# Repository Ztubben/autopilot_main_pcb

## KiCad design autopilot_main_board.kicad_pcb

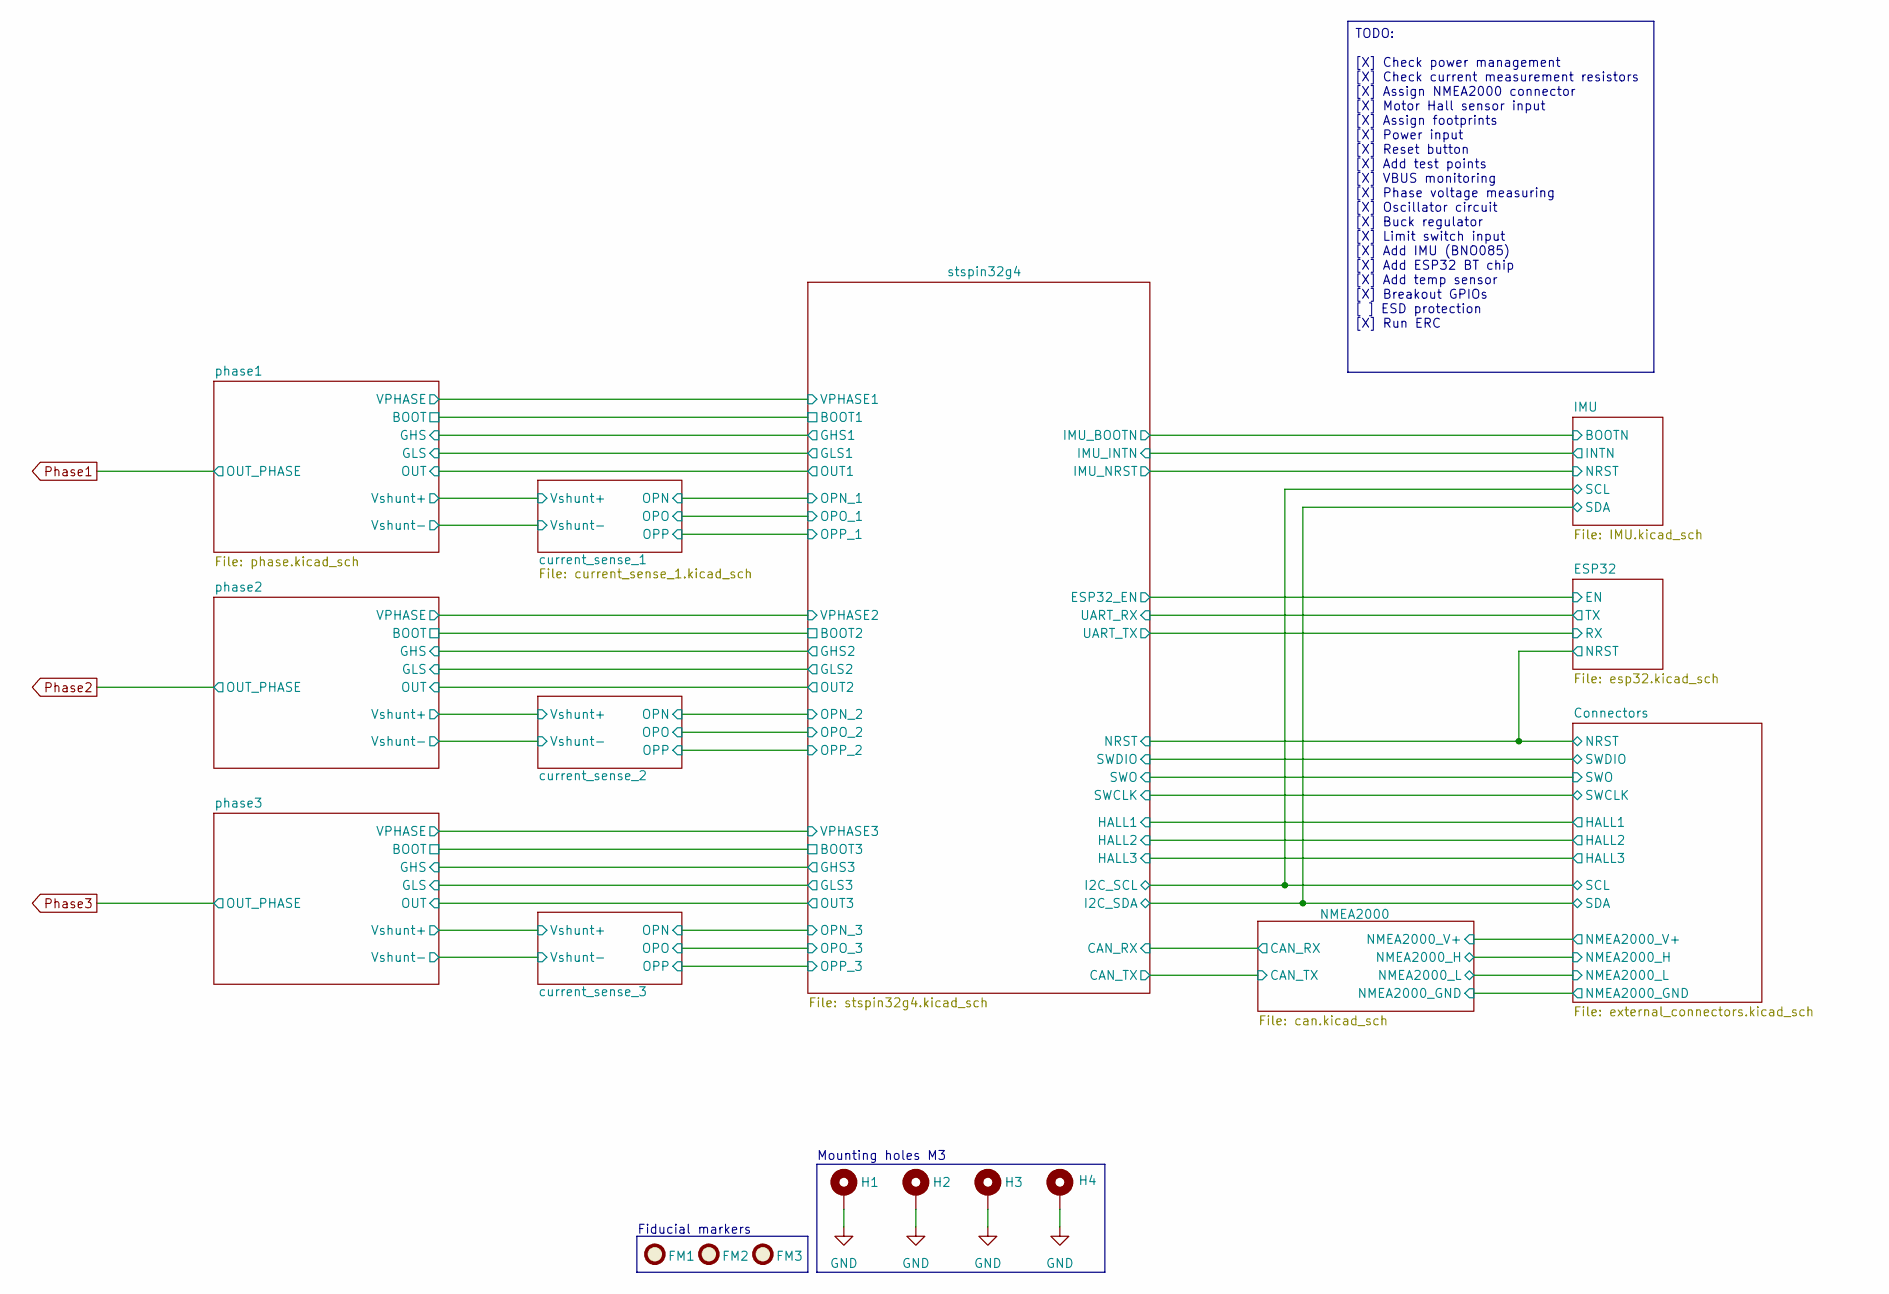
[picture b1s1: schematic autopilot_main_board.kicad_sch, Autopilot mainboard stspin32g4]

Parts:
FM1, FM2, FM3: Fiducial_1mm_Mask2mm
H1, H2, H3, H4: MountingHole_3.2mm_M3_DIN965_Pad

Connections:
GND: H1.1, H2.1, H3.1, H4.1; also elsewhere on the board

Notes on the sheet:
Mounting holes M3
Fiducial markers
TODO: [X] Check power management [X] Check current measurement resistors [X] Assign NMEA2000 connector [X] Motor Hall sensor input [X] Assign footprints [X] Power input [X] Reset button [X] Add test points [X] VBUS monitoring [X] Phase voltage measuring [X] Oscillator circuit [X] Buck regulator [X]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

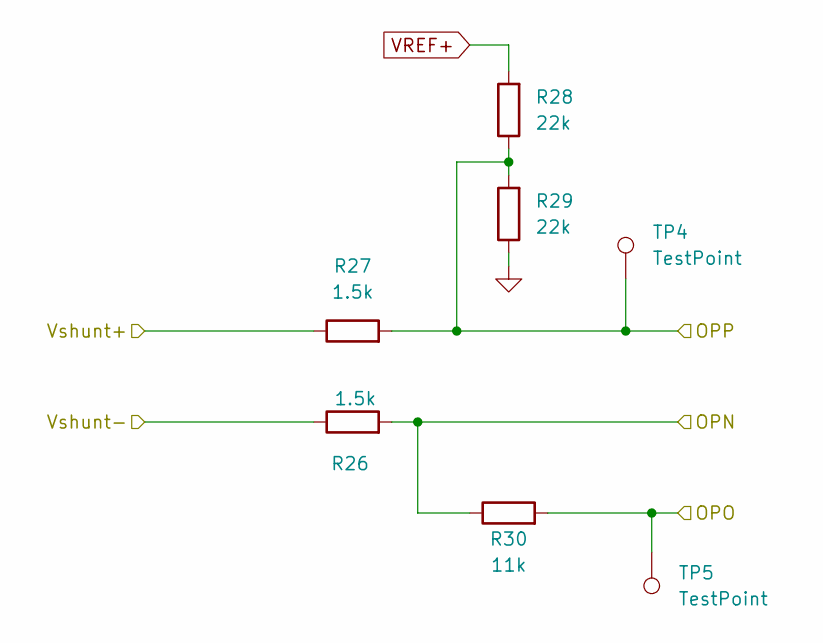
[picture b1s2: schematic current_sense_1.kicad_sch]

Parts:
R26, R27: 1.5k; R_0603_1608Metric
R28, R29: 22k; R_0603_1608Metric
R30: 11k; R_0603_1608Metric
TP4, TP5: TestPoint; TestPoint_Pad_D2.0mm

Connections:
/current_sense_1/OPN: R26.2, R30.1; also elsewhere on the board
/current_sense_1/OPO: R30.2, TP5.1; also elsewhere on the board
/current_sense_1/OPP: R27.2, R28.1, R29.2, TP4.1; also elsewhere on the board
/current_sense_1/Vshunt+: R27.1; also elsewhere on the board
GND: R26.1, R29.1; also elsewhere on the board
VREF+: R28.2; also elsewhere on the board

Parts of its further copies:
R31, R32, R44, R45: 1.5k; R_0603_1608Metric
R33, R34, R46, R47: 22k; R_0603_1608Metric
R35, R48: 11k; R_0603_1608Metric
TP6, TP7, TP8, TP9: TestPoint; TestPoint_Pad_D2.0mm

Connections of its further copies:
/current_sense_2/OPN: R31.2, R35.1; also elsewhere on the board
/current_sense_2/OPO: R35.2, TP7.1; also elsewhere on the board
/current_sense_2/OPP: R32.2, R33.1, R34.2, TP6.1; also elsewhere on the board
/current_sense_2/Vshunt+: R32.1; also elsewhere on the board
/current_sense_3/OPN: R44.2, R48.1; also elsewhere on the board
/current_sense_3/OPO: R48.2, TP9.1; also elsewhere on the board
/current_sense_3/OPP: R45.2, R46.1, R47.2, TP8.1; also elsewhere on the board
/current_sense_3/Vshunt+: R45.1; also elsewhere on the board
GND: R31.1, R34.1, R44.1, R47.1; also elsewhere on the board
VREF+: R33.2, R46.2; also elsewhere on the board

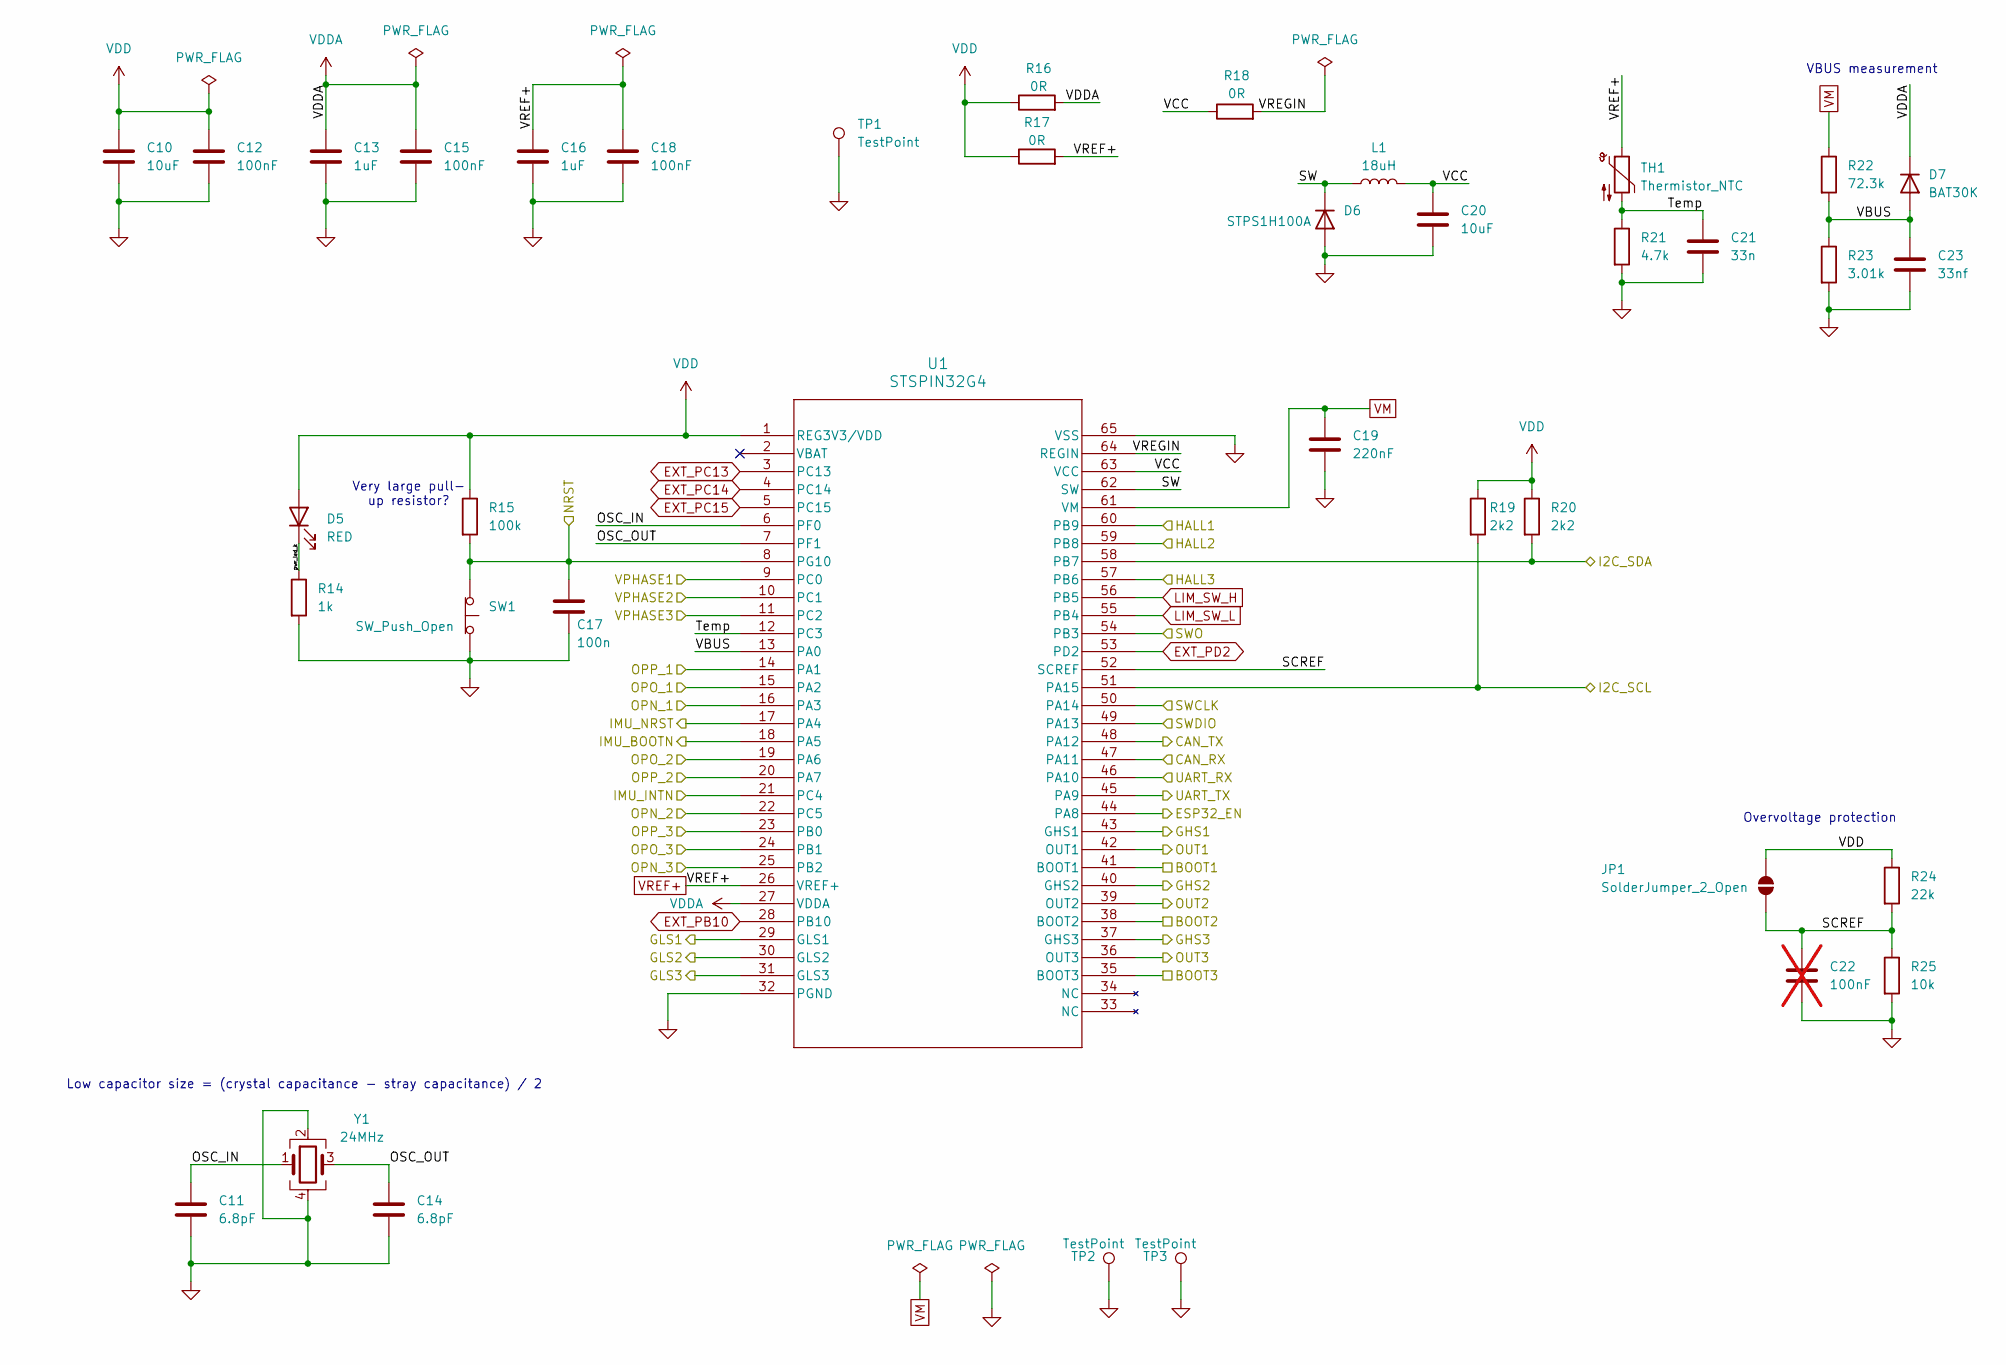
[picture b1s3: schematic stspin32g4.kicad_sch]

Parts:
C10, C20: 10uF; C_1206_3216Metric
C11, C14: 6.8pF; C_1206_3216Metric
C12, C15, C18: 100nF; C_1206_3216Metric
C13, C16: 1uF; C_1206_3216Metric
C17: 100n; C_1206_3216Metric
C19: 220nF; C_1206_3216Metric
C21: 33n; C_1206_3216Metric
C22: 100nF; C_1206_3216Metric; not fitted
C23: 33nf; C_1206_3216Metric
D5: RED; LED_1206_3216Metric
D6: STPS1H100A; D_1206_3216Metric
D7: BAT30K; D_1206_3216Metric
JP1: SolderJumper_2_Open; SolderJumper-2_P1.3mm_Open_RoundedPad1.0x1.5mm
L1: 18uH; L_1206_3216Metric
R14: 1k; R_0603_1608Metric
R15: 100k; R_0603_1608Metric
R16, R17, R18: 0R; R_0603_1608Metric
R19, R20: 2k2; R_0603_1608Metric
R21: 4.7k; R_0603_1608Metric
R22: 72.3k; R_0603_1608Metric
R23: 3.01k; R_0603_1608Metric
R24: 22k; R_0603_1608Metric
R25: 10k; R_0603_1608Metric
SW1: SW_Push_Open; SW_Tactile_Straight_KSA0Axx1LFTR
TH1: Thermistor_NTC; R_1206_3216Metric
TP1, TP2, TP3: TestPoint; TestPoint_Pad_D2.0mm
U1: STSPIN32G4; QFN-64_EP_9.85x9.85_Pitch0.5mm
Y1: 24MHz; Crystal_SMD_3225-4Pin_3.2x2.5mm

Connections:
/Connectors/HALL1: U1.60 (PB9); also elsewhere on the board
/Connectors/HALL2: U1.59 (PB8); also elsewhere on the board
/Connectors/HALL3: U1.57 (PB6); also elsewhere on the board
/Connectors/NRST: C17.1, R15.2, SW1.2 (B), U1.8 (PG10); also elsewhere on the board
/Connectors/SCL: R19.2, U1.51 (PA15); also elsewhere on the board
/Connectors/SDA: R20.2, U1.58 (PB7); also elsewhere on the board
/Connectors/SWCLK: U1.50 (PA14); also elsewhere on the board
/Connectors/SWDIO: U1.49 (PA13); also elsewhere on the board
/Connectors/SWO: U1.54 (PB3); also elsewhere on the board
/ESP32/EN: U1.44 (PA8); also elsewhere on the board
/ESP32/RX: U1.45 (PA9); also elsewhere on the board
/ESP32/TX: U1.46 (PA10); also elsewhere on the board
/IMU/BOOTN: U1.18 (PA5); also elsewhere on the board
/IMU/INTN: U1.21 (PC4); also elsewhere on the board
/IMU/NRST: U1.17 (PA4); also elsewhere on the board
/NMEA2000/CAN_RX: U1.47 (PA11); also elsewhere on the board
/NMEA2000/CAN_TX: U1.48 (PA12); also elsewhere on the board
/current_sense_1/OPN: U1.16 (PA3); also elsewhere on the board
/current_sense_1/OPO: U1.15 (PA2); also elsewhere on the board
/current_sense_1/OPP: U1.14 (PA1); also elsewhere on the board
/current_sense_2/OPN: U1.22 (PC5); also elsewhere on the board
/current_sense_2/OPO: U1.19 (PA6); also elsewhere on the board
/current_sense_2/OPP: U1.20 (PA7); also elsewhere on the board
/current_sense_3/OPN: U1.25 (PB2); also elsewhere on the board
/current_sense_3/OPO: U1.24 (PB1); also elsewhere on the board
/current_sense_3/OPP: U1.23 (PB0); also elsewhere on the board
/phase1/BOOT: U1.41 (BOOT1); also elsewhere on the board
/phase1/GHS: U1.43 (GHS1); also elsewhere on the board
/phase1/GLS: U1.29 (GLS1); also elsewhere on the board
/phase1/VPHASE: U1.9 (PC0); also elsewhere on the board
/phase2/BOOT: U1.38 (BOOT2); also elsewhere on the board
/phase2/GHS: U1.40 (GHS2); also elsewhere on the board
/phase2/GLS: U1.30 (GLS2); also elsewhere on the board
/phase2/VPHASE: U1.10 (PC1); also elsewhere on the board
/phase3/BOOT: U1.35 (BOOT3); also elsewhere on the board
/phase3/GHS: U1.37 (GHS3); also elsewhere on the board
/phase3/GLS: U1.31 (GLS3); also elsewhere on the board
/phase3/VPHASE: U1.11 (PC2); also elsewhere on the board
/stspin32g4/OSC_IN: C11.1, U1.6 (PF0), Y1.1
/stspin32g4/OSC_OUT: C14.1, U1.7 (PF1), Y1.3
/stspin32g4/SCREF: C22.1, JP1.1 (A), R24.2, R25.1, U1.52 (SCREF)
/stspin32g4/SW: D6.1 (K), L1.1, U1.62 (SW)
/stspin32g4/Temp: C21.1, R21.1, TH1.2, U1.12 (PC3)
/stspin32g4/VBUS: C23.1, D7.2 (A), R22.2, R23.1, U1.13 (PA0)
/stspin32g4/VCC: C20.1, L1.2, R18.1, U1.63 (VCC)
/stspin32g4/VREGIN: R18.2, U1.64 (REGIN)
/stspin32g4/pwr_led_k: D5.1 (K), R14.1
EXT_PB10: U1.28 (PB10); also elsewhere on the board
EXT_PC13: U1.3 (PC13); also elsewhere on the board
EXT_PC14: U1.4 (PC14); also elsewhere on the board
EXT_PC15: U1.5 (PC15); also elsewhere on the board
EXT_PD2: U1.53 (PD2); also elsewhere on the board
GND: C10.2, C11.2, C12.2, C13.2, C14.2, C15.2, C16.2, C17.2, C18.2, C19.2, C20.2, C21.2, C22.2, C23.2, D6.2 (A), R14.2, R21.2, R23.2, R25.2, SW1.1 (A), TP1.1, TP2.1, TP3.1, U1.32 (PGND), U1.65 (VSS), Y1.2, Y1.4; also elsewhere on the board
LIM_SW_H: U1.56 (PB5); also elsewhere on the board
LIM_SW_L: U1.55 (PB4); also elsewhere on the board
Phase1: U1.42 (OUT1); also elsewhere on the board
Phase2: U1.39 (OUT2); also elsewhere on the board
Phase3: U1.36 (OUT3); also elsewhere on the board
VDD: C10.1, C12.1, D5.2 (A), JP1.2 (B), R15.1, R16.1, R17.1, R19.1, R20.1, R24.1, U1.1 (REG3V3/VDD); also elsewhere on the board
VDDA: C13.1, C15.1, D7.1 (K), R16.2, U1.27 (VDDA); also elsewhere on the board
VM: C19.1, R22.1, U1.61 (VM); also elsewhere on the board
VREF+: C16.1, C18.1, R17.2, TH1.1, U1.26 (VREF+); also elsewhere on the board

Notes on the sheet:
Low capacitor size = (crystal capacitance - stray capacitance) / 2
VBUS measurement
Very large pull- up resistor?
Overvoltage protection

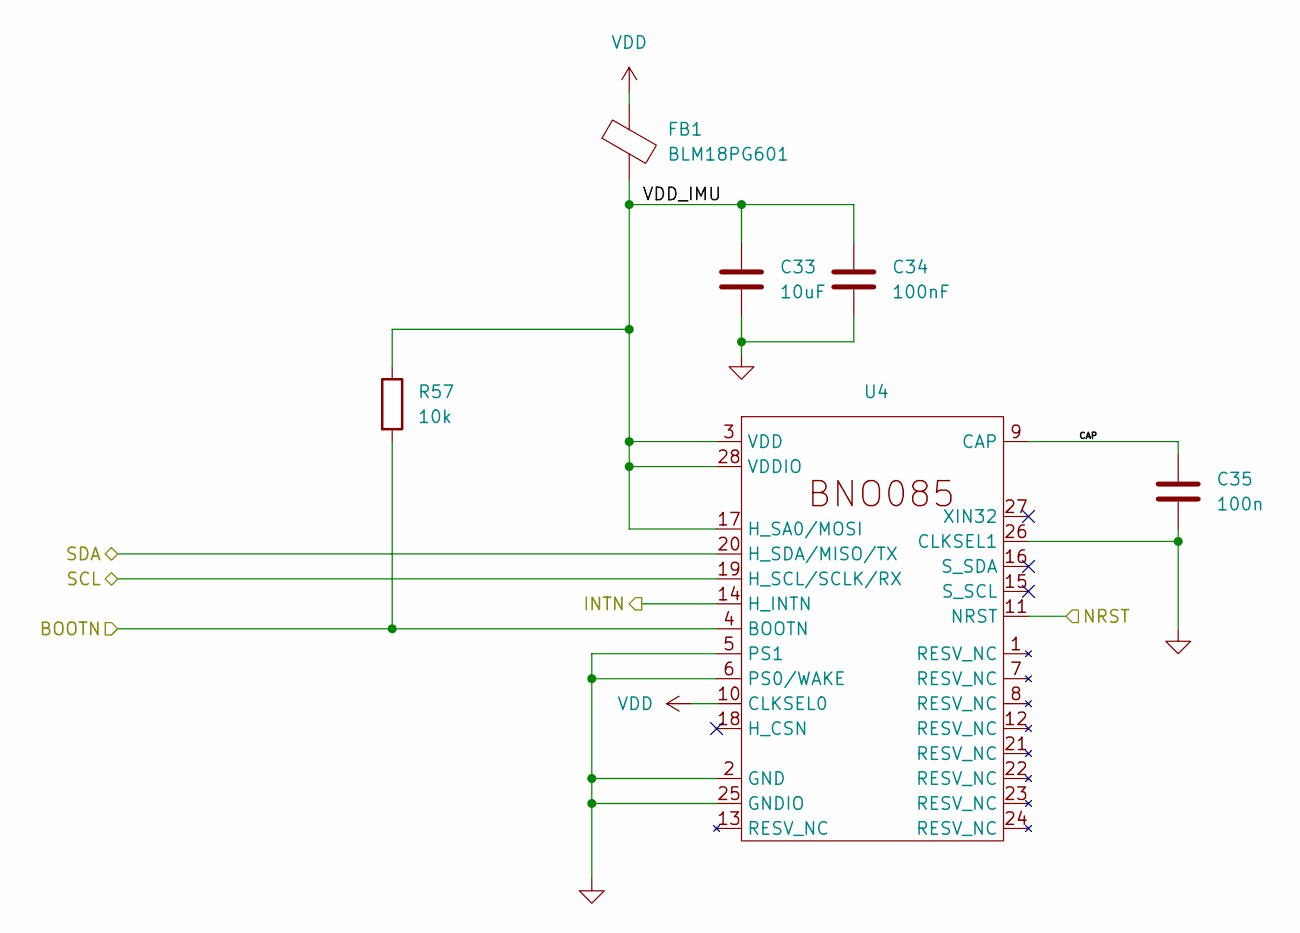
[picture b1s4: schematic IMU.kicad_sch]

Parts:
C33: 10uF; C_1206_3216Metric
C34: 100nF; C_1206_3216Metric
C35: 100n; C_1206_3216Metric
FB1: BLM18PG601; L_1206_3216Metric
R57: 10k; R_0603_1608Metric
U4: BNO085

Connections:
/Connectors/SCL: U4.19 (H_SCL/SCLK/RX); also elsewhere on the board
/Connectors/SDA: U4.20 (H_SDA/MISO/TX); also elsewhere on the board
/IMU/BOOTN: R57.2, U4.4 (BOOTN); also elsewhere on the board
/IMU/CAP: C35.1, U4.9 (CAP)
/IMU/INTN: U4.14 (H_INTN); also elsewhere on the board
/IMU/NRST: U4.11 (NRST); also elsewhere on the board
/IMU/VDD_IMU: C33.1, C34.1, FB1.2, R57.1, U4.3 (VDD), U4.17 (H_SA0/MOSI), U4.28 (VDDIO)
GND: C33.2, C34.2, C35.2, U4.2 (GND), U4.5 (PS1), U4.6 (PS0/WAKE), U4.25 (GNDIO), U4.26 (CLKSEL1); also elsewhere on the board
VDD: FB1.1, U4.10 (CLKSEL0); also elsewhere on the board

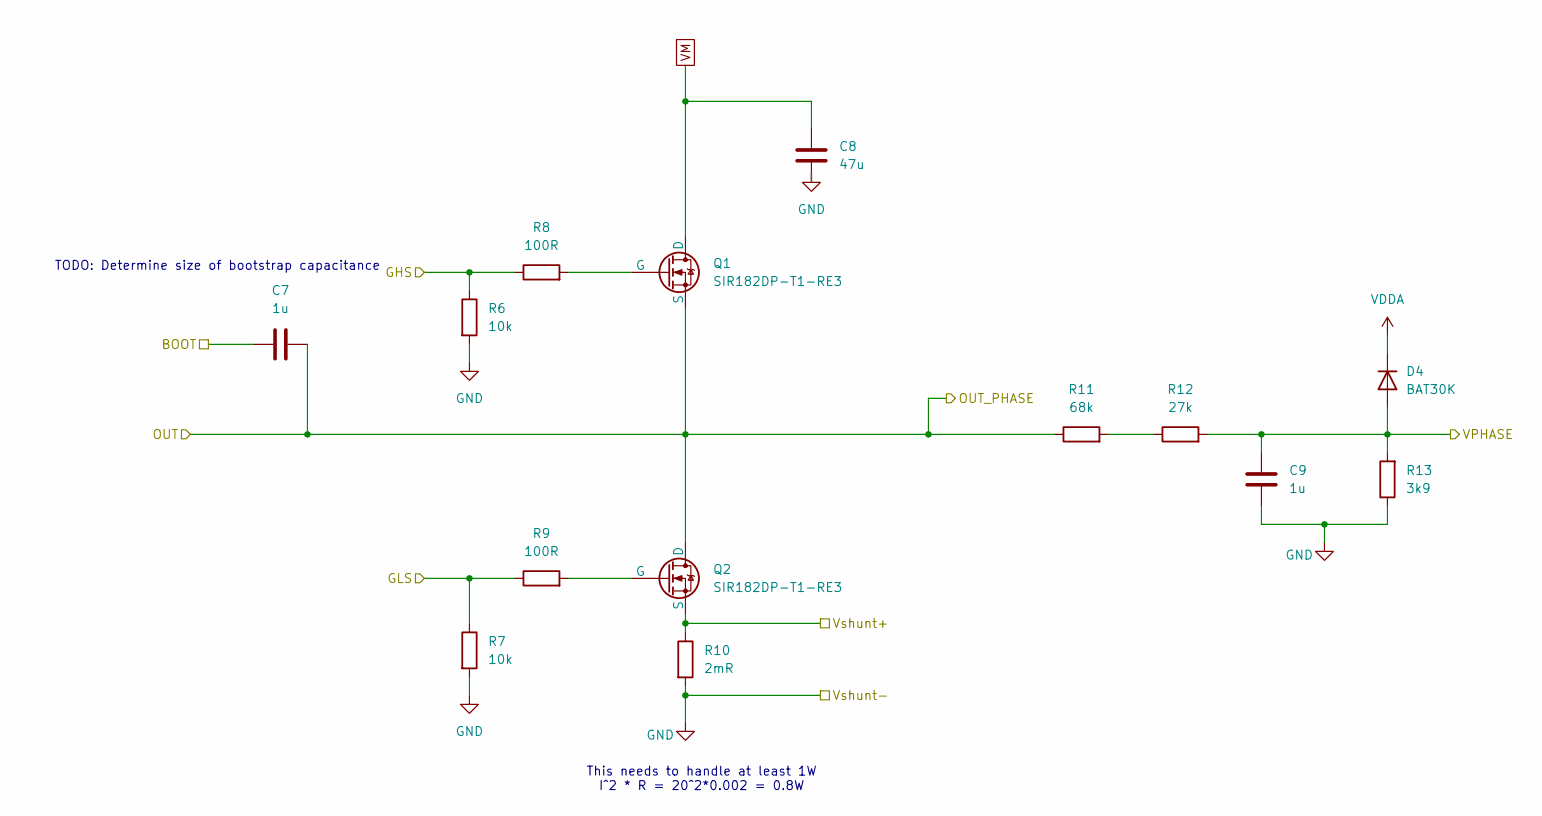
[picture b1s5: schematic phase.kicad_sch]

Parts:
C7, C9: 1u; C_1206_3216Metric
C8: 47u; C_1206_3216Metric
D4: BAT30K; D_1206_3216Metric
Q1, Q2: SIR182DP-T1-RE3; POWERPAK_SO-8_SINGLE_VIS
R6, R7: 10k; R_0603_1608Metric
R8, R9: 100R; R_0603_1608Metric
R10: 2mR; R_0603_1608Metric
R11: 68k; R_0603_1608Metric
R12: 27k; R_0603_1608Metric
R13: 3k9; R_0603_1608Metric

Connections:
/current_sense_1/Vshunt+: Q2.3 (S), R10.1; also elsewhere on the board
/phase1/BOOT: C7.2; also elsewhere on the board
/phase1/GHS: R6.1, R8.1; also elsewhere on the board
/phase1/GLS: R7.1, R9.1; also elsewhere on the board
/phase1/VPHASE: C9.2, D4.2 (A), R12.2, R13.2; also elsewhere on the board
GND: C8.2, C9.1, R6.2, R7.2, R10.2, R13.1; also elsewhere on the board
unnamed: Q1.2 (G), R8.2
unnamed: Q2.2 (G), R9.2
unnamed: R11.2, R12.1
Phase1: C7.1, Q1.3 (S), Q2.1 (D), R11.1; also elsewhere on the board
VDDA: D4.1 (K); also elsewhere on the board
VM: C8.1, Q1.1 (D); also elsewhere on the board

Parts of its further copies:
C26, C28, C29, C31: 1u; C_1206_3216Metric
C27, C30: 47u; C_1206_3216Metric
D8, D9: BAT30K; D_1206_3216Metric
Q3, Q4, Q5, Q6: SIR182DP-T1-RE3; POWERPAK_SO-8_SINGLE_VIS
R36, R37, R49, R50: 10k; R_0603_1608Metric
R38, R39, R51, R52: 100R; R_0603_1608Metric
R40, R53: 2mR; R_0603_1608Metric
R41, R54: 68k; R_0603_1608Metric
R42, R55: 27k; R_0603_1608Metric
R43, R56: 3k9; R_0603_1608Metric

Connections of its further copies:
/current_sense_2/Vshunt+: Q4.3 (S), R40.1; also elsewhere on the board
/current_sense_3/Vshunt+: Q6.3 (S), R53.1; also elsewhere on the board
/phase2/BOOT: C26.2; also elsewhere on the board
/phase2/GHS: R36.1, R38.1; also elsewhere on the board
/phase2/GLS: R37.1, R39.1; also elsewhere on the board
/phase2/VPHASE: C28.2, D8.2 (A), R42.2, R43.2; also elsewhere on the board
/phase3/BOOT: C29.2; also elsewhere on the board
/phase3/GHS: R49.1, R51.1; also elsewhere on the board
/phase3/GLS: R50.1, R52.1; also elsewhere on the board
/phase3/VPHASE: C31.2, D9.2 (A), R55.2, R56.2; also elsewhere on the board
GND: C27.2, C28.1, C30.2, C31.1, R36.2, R37.2, R40.2, R43.1, R49.2, R50.2, R53.2, R56.1; also elsewhere on the board
unnamed: Q3.2 (G), R38.2
unnamed: Q4.2 (G), R39.2
unnamed: Q5.2 (G), R51.2
unnamed: Q6.2 (G), R52.2
unnamed: R41.2, R42.1
unnamed: R54.2, R55.1
Phase2: C26.1, Q3.3 (S), Q4.1 (D), R41.1; also elsewhere on the board
Phase3: C29.1, Q5.3 (S), Q6.1 (D), R54.1; also elsewhere on the board
VDDA: D8.1 (K), D9.1 (K); also elsewhere on the board
VM: C27.1, C30.1, Q3.1 (D), Q5.1 (D); also elsewhere on the board

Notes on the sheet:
This needs to handle at least 1W I^2 * R = 20^2*0.002 = 0.8W
TODO: Determine size of bootstrap capacitance

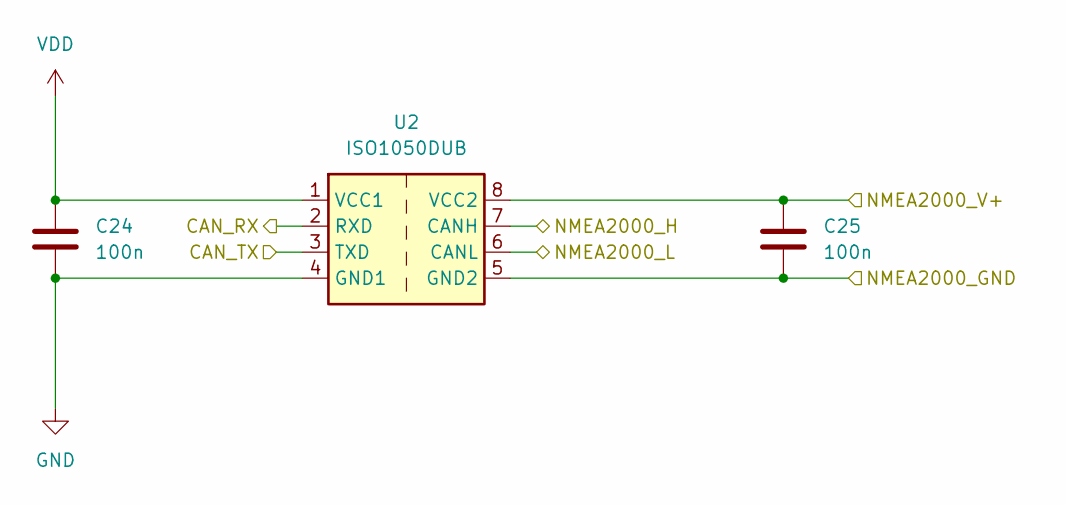
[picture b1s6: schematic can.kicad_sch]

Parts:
C24, C25: 100n; C_1206_3216Metric
U2: ISO1050DUB; SOP-8_6.62x9.15mm_P2.54mm

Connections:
/Connectors/NMEA2000_GND: C25.2, U2.5 (GND2); also elsewhere on the board
/Connectors/NMEA2000_H: U2.7 (CANH); also elsewhere on the board
/Connectors/NMEA2000_L: U2.6 (CANL); also elsewhere on the board
/Connectors/NMEA2000_V+: C25.1, U2.8 (VCC2); also elsewhere on the board
/NMEA2000/CAN_RX: U2.2 (RXD); also elsewhere on the board
/NMEA2000/CAN_TX: U2.3 (TXD); also elsewhere on the board
GND: C24.2, U2.4 (GND1); also elsewhere on the board
VDD: C24.1, U2.1 (VCC1); also elsewhere on the board

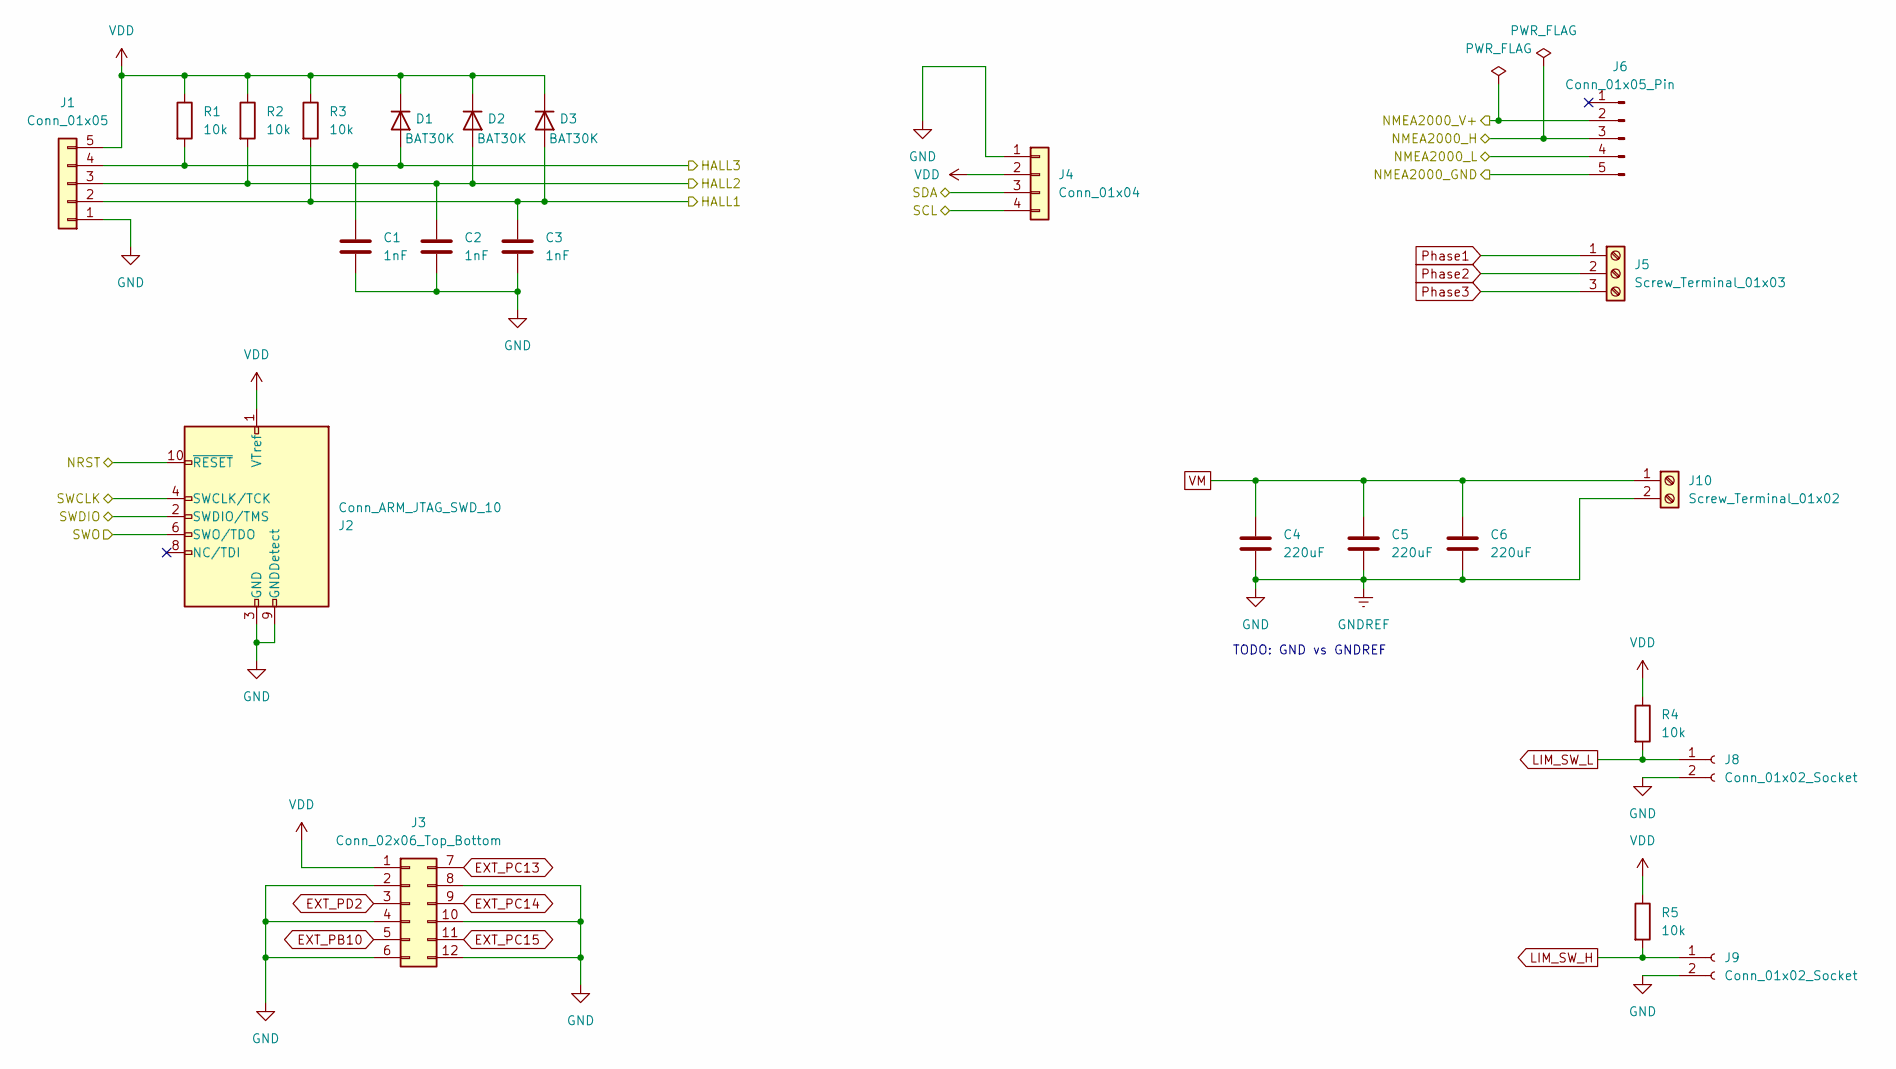
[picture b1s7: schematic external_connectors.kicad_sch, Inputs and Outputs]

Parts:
C1, C2, C3: 1nF; C_1206_3216Metric
C4, C5, C6: 220uF; C_1206_3216Metric
D1, D2, D3: BAT30K; D_1206_3216Metric
J1: Conn_01x05; JST_XH_B5B-XH-A_1x05_P2.50mm_Vertical
J2: Conn_ARM_JTAG_SWD_10; PinHeader_2x05_P1.27mm_Vertical_SMD
J3: Conn_02x06_Top_Bottom; PinHeader_2x06_P2.54mm_Vertical
J4: Conn_01x04; JST_XH_B4B-XH-A_1x04_P2.50mm_Vertical
J5: Screw_Terminal_01x03; TerminalBlock_MaiXu_MX126-5.0-03P_1x03_P5.00mm
J6: Conn_01x05_Pin; JST_XH_B5B-XH-AM_1x05_P2.50mm_Vertical
J8, J9: Conn_01x02_Socket; JST_XH_B2B-XH-AM_1x02_P2.50mm_Vertical
J10: Screw_Terminal_01x02; TerminalBlock_MaiXu_MX126-5.0-02P_1x02_P5.00mm
R1, R2, R3, R4, R5: 10k; R_0603_1608Metric

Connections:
/Connectors/HALL1: C3.1, D3.2 (A), J1.2, R3.2; also elsewhere on the board
/Connectors/HALL2: C2.1, D2.2 (A), J1.3, R2.2; also elsewhere on the board
/Connectors/HALL3: C1.1, D1.2 (A), J1.4, R1.2; also elsewhere on the board
/Connectors/NMEA2000_GND: J6.5; also elsewhere on the board
/Connectors/NMEA2000_H: J6.3; also elsewhere on the board
/Connectors/NMEA2000_L: J6.4; also elsewhere on the board
/Connectors/NMEA2000_V+: J6.2; also elsewhere on the board
/Connectors/NRST: J2.10 (~RESET); also elsewhere on the board
/Connectors/SCL: J4.4; also elsewhere on the board
/Connectors/SDA: J4.3; also elsewhere on the board
/Connectors/SWCLK: J2.4 (SWCLK/TCK); also elsewhere on the board
/Connectors/SWDIO: J2.2 (SWDIO/TMS); also elsewhere on the board
/Connectors/SWO: J2.6 (SWO/TDO); also elsewhere on the board
EXT_PB10: J3.5; also elsewhere on the board
EXT_PC13: J3.7; also elsewhere on the board
EXT_PC14: J3.9; also elsewhere on the board
EXT_PC15: J3.11; also elsewhere on the board
EXT_PD2: J3.3; also elsewhere on the board
GND: C1.2, C2.2, C3.2, C4.2, C5.2, C6.2, J1.1, J2.3 (GND), J2.5 (GND), J2.9 (GNDDetect), J3.2, J3.4, J3.6, J3.8, J3.10, J3.12, J4.1, J8.2, J9.2, J10.2; also elsewhere on the board
LIM_SW_H: J9.1, R5.2; also elsewhere on the board
LIM_SW_L: J8.1, R4.2; also elsewhere on the board
Phase1: J5.1; also elsewhere on the board
Phase2: J5.2; also elsewhere on the board
Phase3: J5.3; also elsewhere on the board
VDD: D1.1 (K), D2.1 (K), D3.1 (K), J1.5, J2.1 (VTref), J3.1, J4.2, R1.1, R2.1, R3.1, R4.1, R5.1; also elsewhere on the board
VM: C4.1, C5.1, C6.1, J10.1; also elsewhere on the board

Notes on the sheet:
TODO: GND vs GNDREF

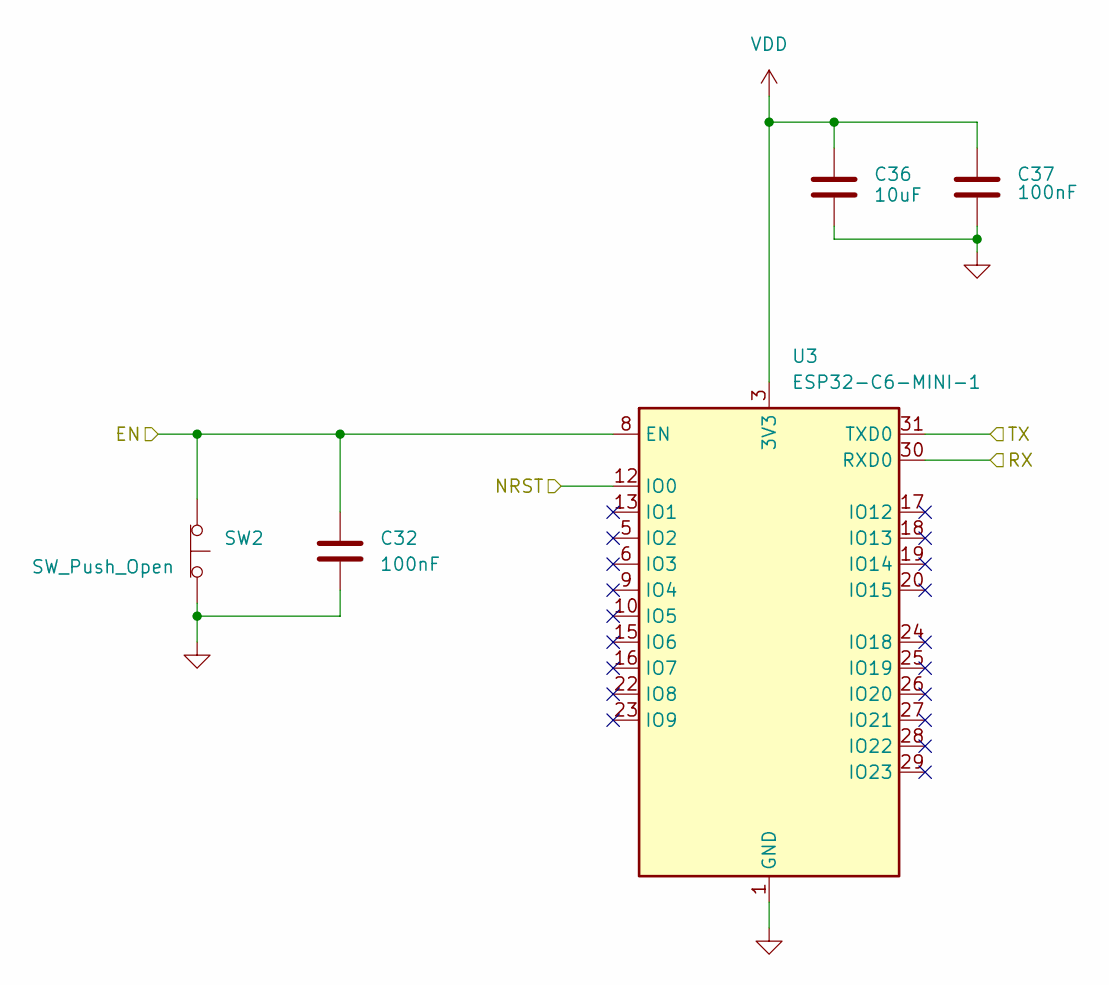
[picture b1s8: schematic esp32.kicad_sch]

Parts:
C32, C37: 100nF; C_1206_3216Metric
C36: 10uF; C_1206_3216Metric
SW2: SW_Push_Open; SW_Tactile_Straight_KSA0Axx1LFTR
U3: ESP32-C6-MINI-1

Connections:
/Connectors/NRST: U3.12 (IO0); also elsewhere on the board
/ESP32/EN: C32.1, SW2.2 (B), U3.8 (EN); also elsewhere on the board
/ESP32/RX: U3.30 (RXD0); also elsewhere on the board
/ESP32/TX: U3.31 (TXD0); also elsewhere on the board
GND: C32.2, C36.2, C37.2, SW2.1 (A), U3.1 (GND), U3.2 (GND), U3.11 (GND), U3.14 (GND), U3.36 (GND), U3.37 (GND), U3.38 (GND), U3.39 (GND), U3.40 (GND), U3.41 (GND), U3.42 (GND), U3.43 (GND), U3.44 (GND), U3.45 (GND), U3.46 (GND), U3.47 (GND), U3.48 (GND), U3.49 (GND), U3.50 (GND), U3.51 (GND), U3.52 (GND), U3.53 (GND); also elsewhere on the board
VDD: C36.1, C37.1, U3.3 (3V3); also elsewhere on the board

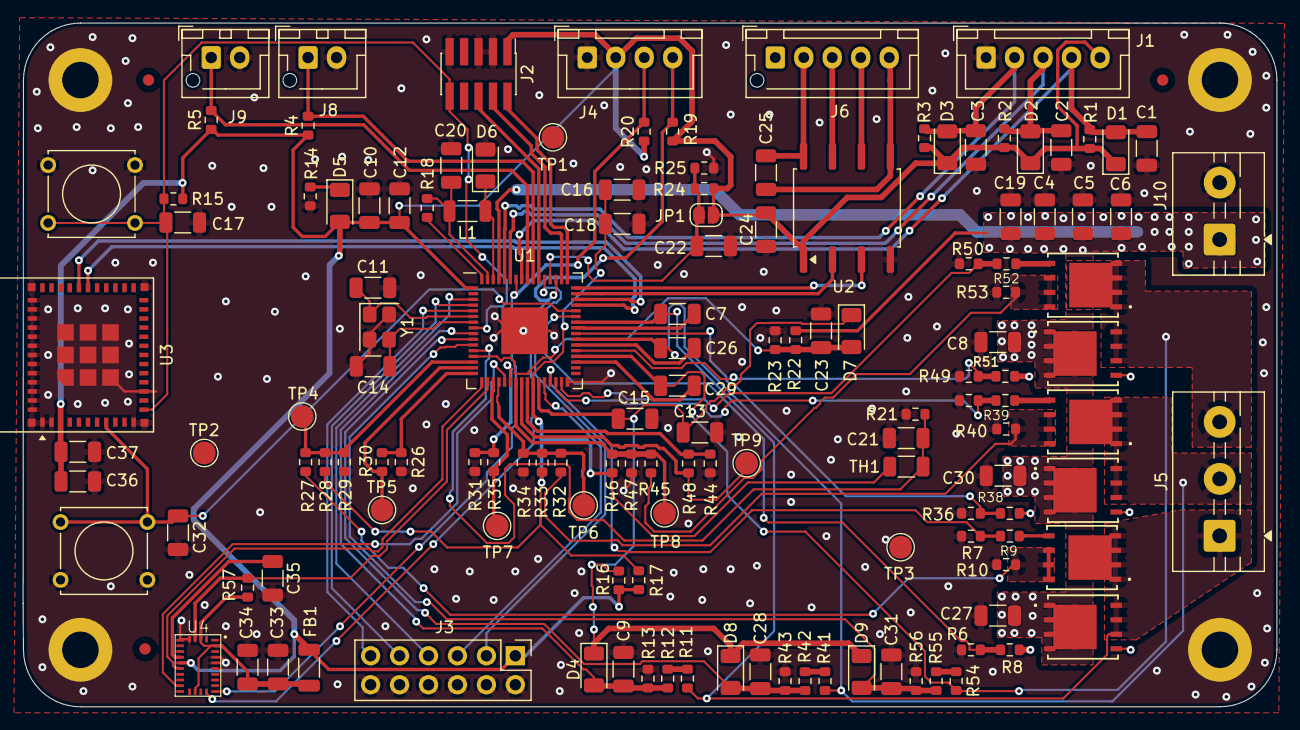
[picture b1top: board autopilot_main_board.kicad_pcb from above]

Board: 4 copper layers, 110.0 x 60.0 mm, 145 parts (0 on the bottom side), 80 nets.

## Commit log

2026-03-14 Add kicad project
2026-03-17 Remove unused files
2026-03-22 Initial PCB layout
2026-03-24 Continued routing
2026-03-26 Routing complete
2026-03-28 DRC check completed
